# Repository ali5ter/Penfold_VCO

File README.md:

# Penfold_VCO
[KiCad](https://www.kicad.org/) project for the circuit and PCB of R.A. Penfolds VCO design which I adapted as a Eurorack powered module.
The original circuit is taken from [the book, "Electronic Synthesiser Construction" by R. A. Penfold](https://sdiy.info/wiki/Penfold_synthesiser), published by Babani in 1986.

I have kept to the original design as much as possible, but added power and switched INT.CV via [a Eurorack spec bus](https://doepfer.de/a100_man/a100t_e.htm).

The circuit and PCB are verfied to work and being used as part of my modular build.

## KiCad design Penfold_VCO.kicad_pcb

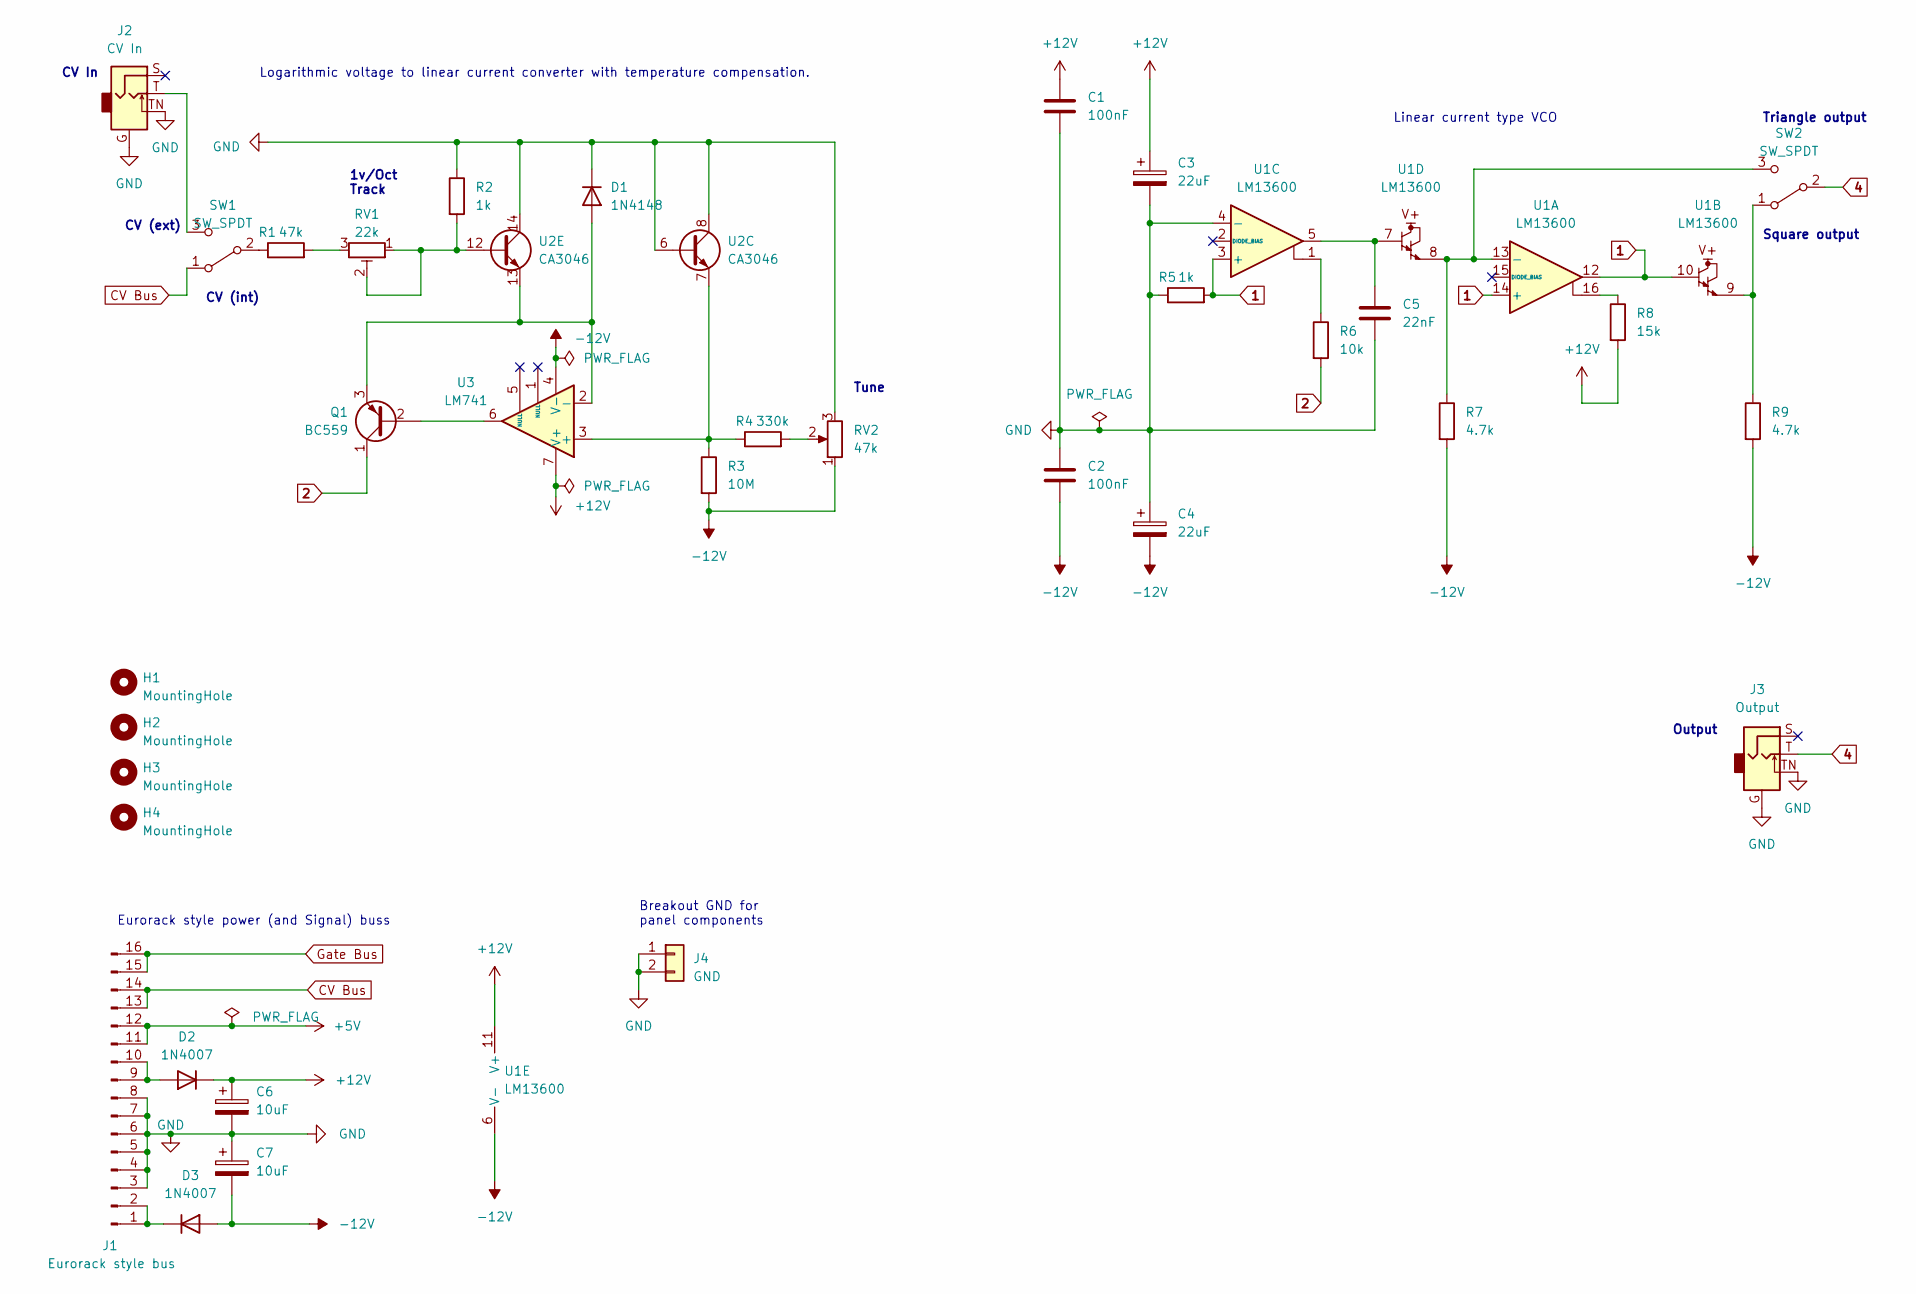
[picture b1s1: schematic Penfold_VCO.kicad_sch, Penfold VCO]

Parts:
C1, C2: 100nF; C_Disc_D5.0mm_W2.5mm_P5.00mm
C3, C4: 22uF; CP_Radial_D5.0mm_P2.00mm
C5: 22nF; C_Disc_D5.0mm_W2.5mm_P5.00mm
C6, C7: 10uF; CP_Radial_D5.0mm_P2.00mm
D1: 1N4148; D_DO-35_SOD27_P7.62mm_Horizontal
D2, D3: 1N4007; D_DO-41_SOD81_P10.16mm_Horizontal
H1, H2, H4: MountingHole; MountingHole_3.2mm_M3
H3: MountingHole; MountingHole_3mm
J1: Eurorack style bus; PinHeader_2x08_P2.54mm_Vertical
J2: CV In
J3: Output
J4: GND; PinHeader_1x02_P2.54mm_Vertical
Q1: BC559; TO-92_Inline
R1: 47k; R_Axial_DIN0207_L6.3mm_D2.5mm_P10.16mm_Horizontal
R2, R5: 1k; R_Axial_DIN0207_L6.3mm_D2.5mm_P10.16mm_Horizontal
R3: 10M; R_Axial_DIN0207_L6.3mm_D2.5mm_P10.16mm_Horizontal
R4: 330k; R_Axial_DIN0207_L6.3mm_D2.5mm_P10.16mm_Horizontal
R6: 10k; R_Axial_DIN0207_L6.3mm_D2.5mm_P10.16mm_Horizontal
R7, R9: 4.7k; R_Axial_DIN0207_L6.3mm_D2.5mm_P10.16mm_Horizontal
R8: 15k; R_Axial_DIN0207_L6.3mm_D2.5mm_P10.16mm_Horizontal
RV1: 22k; PinHeader_1x03_P2.54mm_Vertical
RV2: 47k; PinHeader_1x03_P2.54mm_Vertical
SW1, SW2: SW_SPDT; PinHeader_1x03_P2.54mm_Vertical
U1: LM13600; DIP-16_W7.62mm_Socket_LongPads
U2: CA3046; DIP-14_W7.62mm_Socket_LongPads
U3: LM741; DIP-8_W7.62mm_Socket_LongPads

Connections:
1: R5.2, U1.3 (+), U1.10, U1.12, U1.14 (+)
2: Q1.1 (C), R6.2
4: J3.T, SW2.2 (B)
+5V: J1.11, J1.12
+12V: C1.1, C3.1, C6.1, D2.1 (K), R8.2, U1.11 (V+), U3.7 (V+)
-12V: C2.2, C4.2, C7.2, D3.2 (A), R3.2, R7.2, R9.2, RV2.1, U1.6 (V-), U3.4 (V-)
CV Bus: J1.13, J1.14, SW1.1 (A)
GND: C1.2, C2.1, C3.2, C4.1, C5.2, C6.2, C7.1, D1.1 (K), J1.3, J1.4, J1.5, J1.6, J1.7, J1.8, J2.G, J2.TN, J3.G, J3.TN, J4.1, J4.2, R2.1, R5.1, RV2.3, U1.4 (-), U2.6 (B3), U2.8 (C3), U2.14 (C5)
Gate Bus: J1.15, J1.16
unnamed: C5.1, U1.5, U1.7
unnamed: D1.2 (A), Q1.3 (E), U2.13 (E5), U3.2 (-)
unnamed: D2.2 (A), J1.9, J1.10
unnamed: D3.1 (K), J1.1, J1.2
unnamed: Q1.2 (B), U3.6
unnamed: R1.2, RV1.3
unnamed: R4.2, RV2.2
unnamed: R6.1, U1.1
unnamed: R8.1, U1.16
unnamed: R1.1, SW1.2 (B)
unnamed: J2.T, SW1.3 (C)
unnamed: R9.1, SW2.1 (A), U1.9
unnamed: R7.1, SW2.3 (C), U1.8, U1.13 (-)
unnamed: R3.1, R4.1, U2.7 (E3), U3.3 (+)
unnamed: R2.2, RV1.1, RV1.2, U2.12 (B5)

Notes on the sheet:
CV In
Linear current type VCO
CV (ext)
Eurorack style power (and Signal) buss
CV (int)
Triangle output
Output
Tune
Breakout GND for panel components
Logarithmic voltage to linear current converter with temperature compensation.
Square output
1v/Oct Track

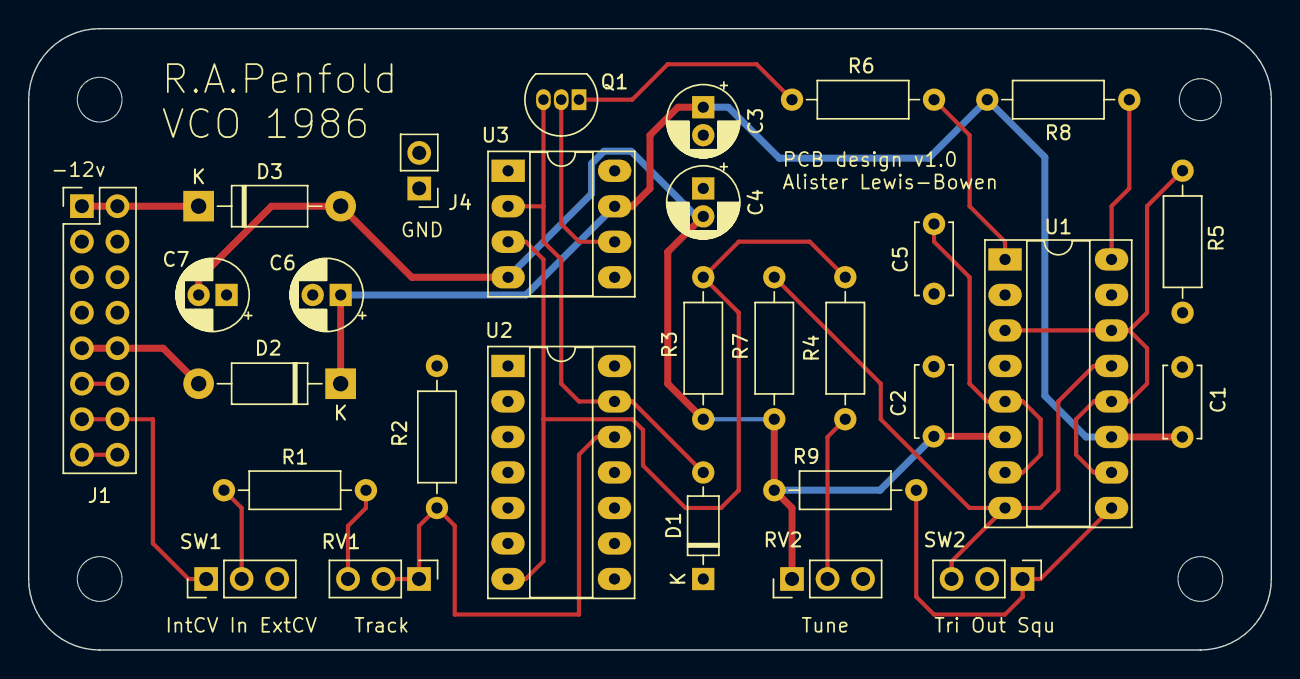
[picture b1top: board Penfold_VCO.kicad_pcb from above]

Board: 2 copper layers, 88.9 x 44.5 mm, 33 parts (0 on the bottom side), 22 nets.

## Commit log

2023-06-01 Update README.md
    Added to readme
2023-06-01 igrate to new repo
2023-06-02 Update README.md
    fix link
